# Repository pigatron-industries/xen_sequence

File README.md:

# xen_sequence
MIDI hardware sequencer

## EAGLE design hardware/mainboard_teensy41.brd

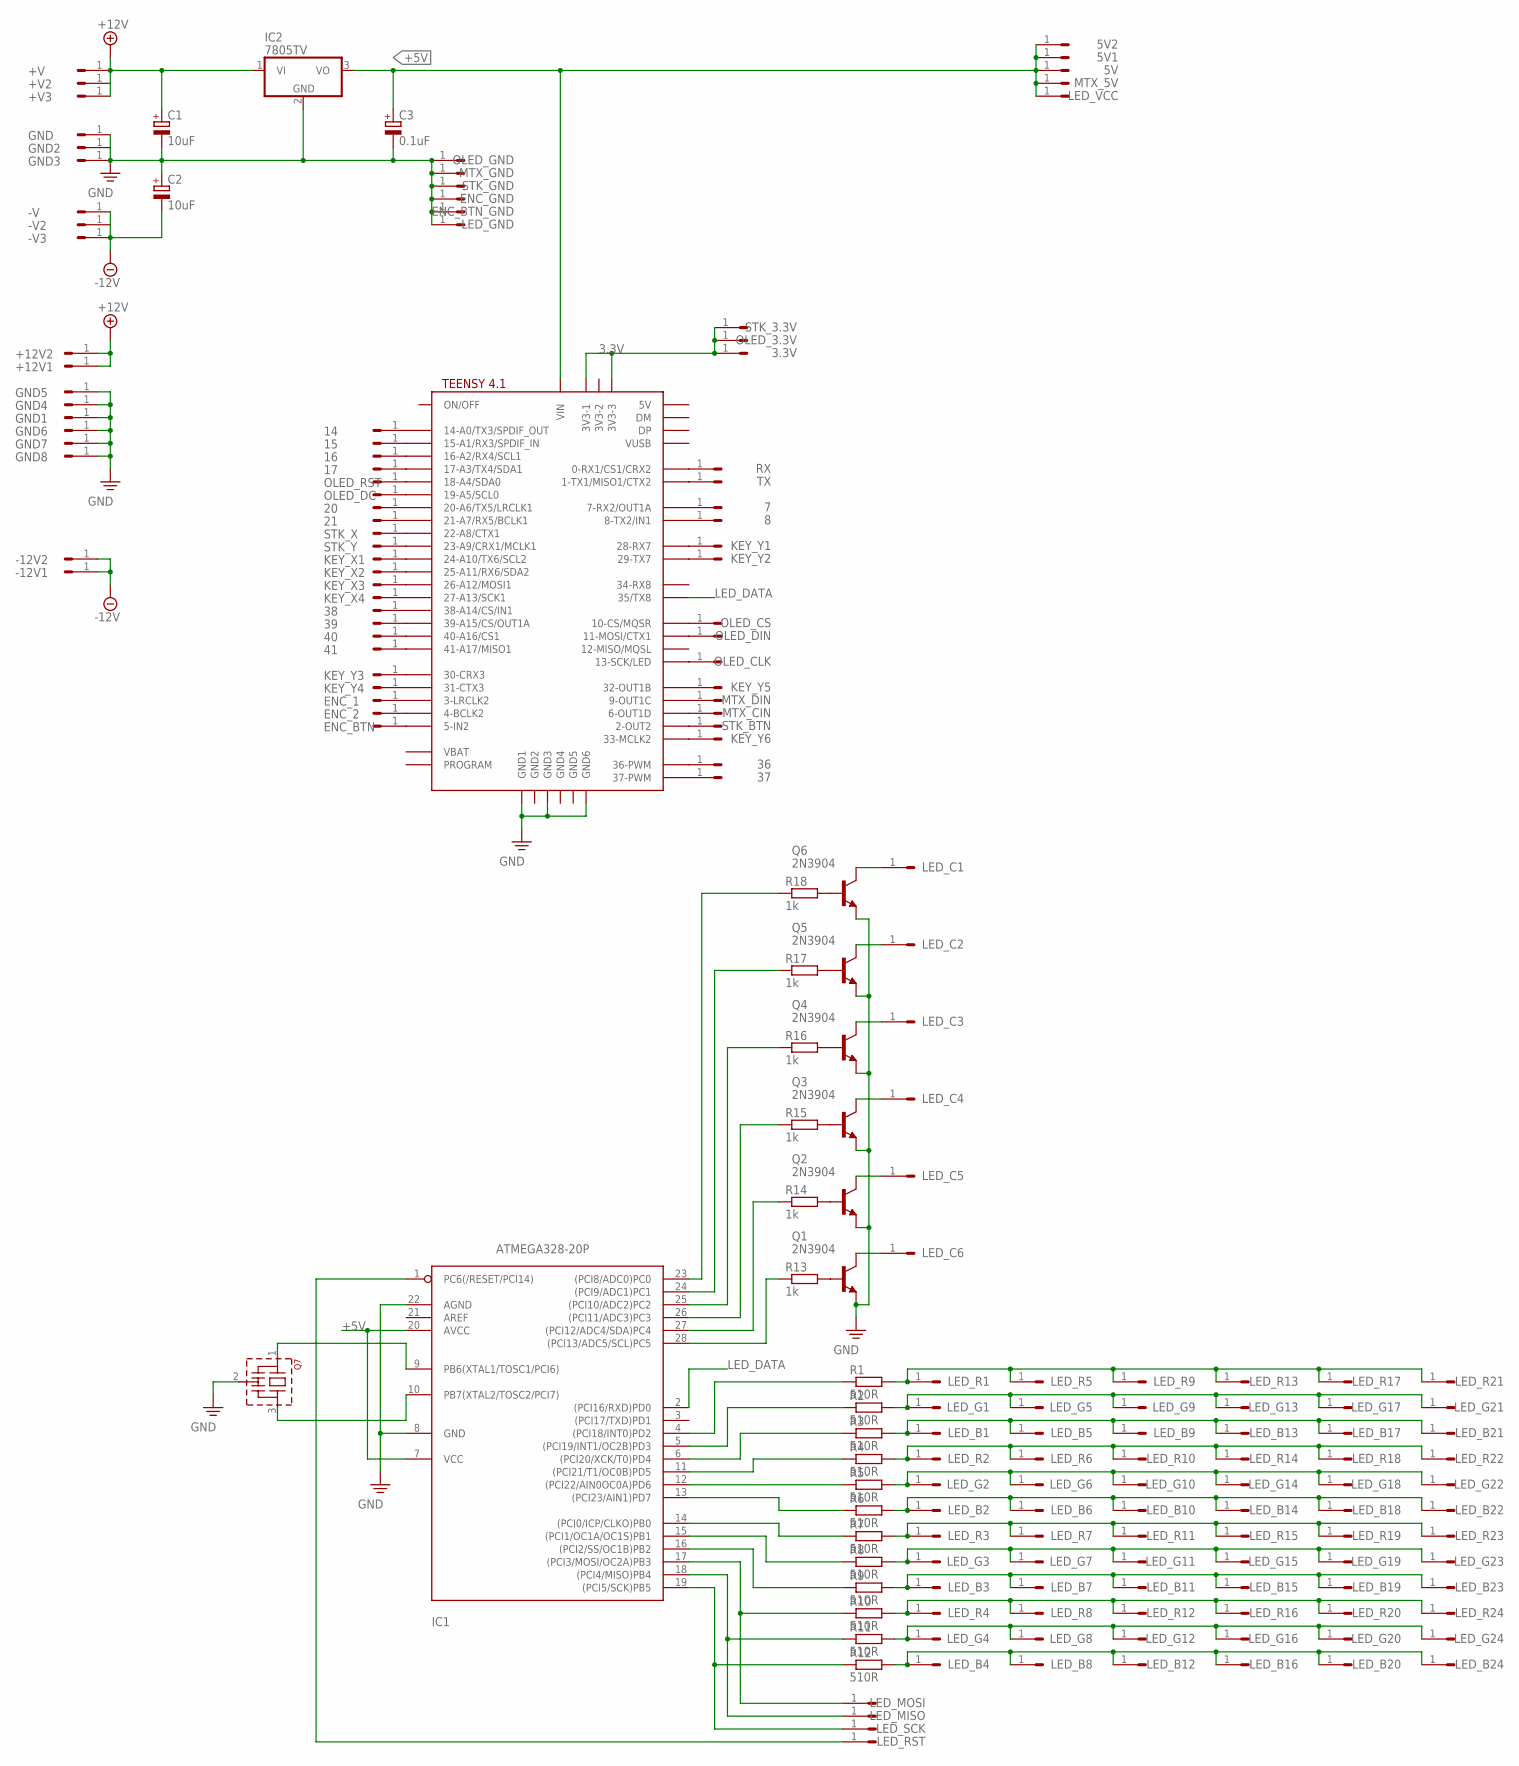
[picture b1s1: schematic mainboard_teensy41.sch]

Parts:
3.3V, 5V, 5V1, 5V2, 7, 8, 14, 15, 16, 17, 20, 21, 36, 37, 38, 39, 40, 41: HEADER/MALE/01
+12V1, +12V2: HEADER/MALE/01
+V, +V2, +V3: HEADER/MALE/01
-12V1, -12V2: HEADER/MALE/01
-V, -V2, -V3: HEADER/MALE/01
C1, C2: 10uF; E2,5-6
C3: 0.1uF; E2,5-6
ENC_1, ENC_2: HEADER/MALE/01
ENC_BTN: HEADER/MALE/01
ENC_BTN_GND: HEADER/MALE/01
ENC_GND: HEADER/MALE/01
GND, GND1, GND2, GND3, GND4, GND5, GND6, GND7, GND8: HEADER/MALE/01
IC1: ATMEGA328-20P; DIL28-3
IC2: 7805TV; TO220V
KEY_X1, KEY_X2, KEY_X3, KEY_X4: HEADER/MALE/01
KEY_Y1, KEY_Y2, KEY_Y3, KEY_Y4, KEY_Y5, KEY_Y6: HEADER/MALE/01
LED_B1, LED_B2, LED_B3, LED_B4, LED_B5, LED_B6, LED_B7, LED_B8, LED_B9, LED_B10, LED_B11, LED_B12, LED_B13, LED_B14, LED_B15, LED_B16, LED_B17, LED_B18, LED_B19, LED_B20, LED_B21, LED_B22, LED_B23, LED_B24: HEADER/MALE/01
LED_C1, LED_C2, LED_C3, LED_C4, LED_C5, LED_C6: HEADER/MALE/01
LED_G1, LED_G2, LED_G3, LED_G4, LED_G5, LED_G6, LED_G7, LED_G8, LED_G9, LED_G10, LED_G11, LED_G12, LED_G13, LED_G14, LED_G15, LED_G16, LED_G17, LED_G18, LED_G19, LED_G20, LED_G21, LED_G22, LED_G23, LED_G24: HEADER/MALE/01
LED_GND: HEADER/MALE/01
LED_MISO: HEADER/MALE/01
LED_MOSI: HEADER/MALE/01
LED_R1, LED_R2, LED_R3, LED_R4, LED_R5, LED_R6, LED_R7, LED_R8, LED_R9, LED_R10, LED_R11, LED_R12, LED_R13, LED_R14, LED_R15, LED_R16, LED_R17, LED_R18, LED_R19, LED_R20, LED_R21, LED_R22, LED_R23, LED_R24: HEADER/MALE/01
LED_RST: HEADER/MALE/01
LED_SCK: HEADER/MALE/01
LED_VCC: HEADER/MALE/01
MTX_5V: HEADER/MALE/01
MTX_CIN: HEADER/MALE/01
MTX_DIN: HEADER/MALE/01
MTX_GND: HEADER/MALE/01
OLED_3.3V: HEADER/MALE/01
OLED_CLK: HEADER/MALE/01
OLED_CS: HEADER/MALE/01
OLED_DC: HEADER/MALE/01
OLED_DIN: HEADER/MALE/01
OLED_GND: HEADER/MALE/01
OLED_RST: HEADER/MALE/01
Q1, Q2, Q3, Q4, Q5, Q6: 2N3904; TO92
Q7: CSTLS_G; CSTLS_G8
R1, R2, R3, R4, R5, R6, R7, R8, R9, R10, R11, R12: 510R; RESISTOR/7.5
R13, R14, R15, R16, R17, R18: 1k; RESISTOR/7.5
RX: HEADER/MALE/01
STK_3.3V: HEADER/MALE/01
STK_BTN: HEADER/MALE/01
STK_GND: HEADER/MALE/01
STK_X: HEADER/MALE/01
STK_Y: HEADER/MALE/01
TX: HEADER/MALE/01
U$1: TEENSY41-E; TENNSY41-E

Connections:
3.3V: 3.3V.1, OLED_3.3V.1, STK_3.3V.1, U$1.3V3-1, U$1.3V3-3
+5V: 5V.1, 5V1.1, 5V2.1, C3.+, IC1.7 (VCC), IC1.20 (AVCC), IC2.3 (VO), LED_VCC.1, MTX_5V.1, U$1.VIN
+12V: +12V1.1, +12V2.1, +V.1, +V2.1, +V3.1, C1.+, IC2.1 (VI)
-12V: -12V1.1, -12V2.1, -V.1, -V2.1, -V3.1, C2.-
GND: C1.-, C2.+, C3.-, ENC_BTN_GND.1, ENC_GND.1, GND.1, GND1.1, GND2.1, GND3.1, GND4.1, GND5.1, GND6.1, GND7.1, GND8.1, IC1.8 (GND), IC1.22 (AGND), IC2.2 (GND), LED_GND.1, MTX_GND.1, OLED_GND.1, Q1.3 (E), Q2.3 (E), Q3.3 (E), Q4.3 (E), Q5.3 (E), Q6.3 (E), Q7.2 (VSS), STK_GND.1, U$1.GND1, U$1.GND3, U$1.GND6
LED_DATA: IC1.2 ((PCI16/RXD)PD0), U$1.35-TX8 (35/TX8)
unnamed: IC1.4 ((PCI18/INT0)PD2), R1.1
unnamed: OLED_CS.1, U$1.10-CS\MQSR (10-CS/MQSR)
unnamed: OLED_DIN.1, U$1.11-MOSI/CTX1
unnamed: OLED_CLK.1, U$1.13-SCK/LED
unnamed: RX.1, U$1.0-RX1/CS1/CRX2
unnamed: TX.1, U$1.1-TX1/MISO1/CTX2
unnamed: KEY_X1.1, U$1.24-A10/TX6/SCL2
unnamed: KEY_X2.1, U$1.25-A11/RX6/SDA2
unnamed: KEY_Y1.1, U$1.28-RX7
unnamed: KEY_Y2.1, U$1.29-TX7
unnamed: KEY_Y5.1, U$1.32-OUT1B
unnamed: KEY_X3.1, U$1.26-A12/MOSI1
unnamed: MTX_CIN.1, U$1.6-OUT1D
unnamed: STK_BTN.1, U$1.2-OUT2
unnamed: KEY_Y6.1, U$1.33-MCLK2
unnamed: KEY_Y3.1, U$1.30-CRX3
unnamed: KEY_Y4.1, U$1.31-CTX3
unnamed: ENC_1.1, U$1.3-LRCLK2
unnamed: ENC_2.1, U$1.4-BCLK2
unnamed: ENC_BTN.1, U$1.5-IN2
unnamed: KEY_X4.1, U$1.27-A13/SCK1
unnamed: STK_X.1, U$1.22-A8/CTX1
unnamed: STK_Y.1, U$1.23-A9/CRX1/MCLK1
unnamed: OLED_RST.1, U$1.18-A4/SDA0
unnamed: OLED_DC.1, U$1.19-A5/SCL0
unnamed: 14.1, U$1.14-A0/TX3/SPDIF_OUT
unnamed: IC1.5 ((PCI19/INT1/OC2B)PD3), R2.1
unnamed: IC1.6 ((PCI20/XCK/T0)PD4), R3.1
unnamed: IC1.11 ((PCI21/T1/OC0B)PD5), R4.1
unnamed: IC1.12 ((PCI22/AIN0OC0A)PD6), R5.1
unnamed: IC1.13 ((PCI23/AIN1)PD7), R6.1
unnamed: IC1.14 ((PCI0/ICP/CLKO)PB0), R7.1
unnamed: IC1.15 ((PCI1/OC1A/OC1S)PB1), R8.1
unnamed: IC1.16 ((PCI2/SS/OC1B)PB2), R9.1
unnamed: IC1.17 ((PCI3/MOSI/OC2A)PB3), LED_MOSI.1, R10.1
unnamed: IC1.18 ((PCI4/MISO)PB4), LED_MISO.1, R11.1
unnamed: 15.1, U$1.15-A1/RX3/SPDIF_IN
unnamed: IC1.1 (PC6(/RESET/PCI14)), LED_RST.1
unnamed: LED_R1.1, LED_R5.1, LED_R9.1, LED_R13.1, LED_R17.1, LED_R21.1, R1.2
unnamed: LED_G1.1, LED_G5.1, LED_G9.1, LED_G13.1, LED_G17.1, LED_G21.1, R2.2
unnamed: LED_B1.1, LED_B5.1, LED_B9.1, LED_B13.1, LED_B17.1, LED_B21.1, R3.2
unnamed: LED_R2.1, LED_R6.1, LED_R10.1, LED_R14.1, LED_R18.1, LED_R22.1, R4.2
unnamed: LED_G2.1, LED_G6.1, LED_G10.1, LED_G14.1, LED_G18.1, LED_G22.1, R5.2
unnamed: LED_B2.1, LED_B6.1, LED_B10.1, LED_B14.1, LED_B18.1, LED_B22.1, R6.2
unnamed: LED_R3.1, LED_R7.1, LED_R11.1, LED_R15.1, LED_R19.1, LED_R23.1, R7.2
unnamed: LED_G3.1, LED_G7.1, LED_G11.1, LED_G15.1, LED_G19.1, LED_G23.1, R8.2
unnamed: LED_B3.1, LED_B7.1, LED_B11.1, LED_B15.1, LED_B19.1, LED_B23.1, R9.2
unnamed: LED_R4.1, LED_R8.1, LED_R12.1, LED_R16.1, LED_R20.1, LED_R24.1, R10.2
unnamed: LED_G4.1, LED_G8.1, LED_G12.1, LED_G16.1, LED_G20.1, LED_G24.1, R11.2
unnamed: LED_B4.1, LED_B8.1, LED_B12.1, LED_B16.1, LED_B20.1, LED_B24.1, R12.2
unnamed: Q1.2 (B), R13.2
unnamed: IC1.28 ((PCI13/ADC5/SCL)PC5), R13.1
unnamed: Q2.2 (B), R14.2
unnamed: Q3.2 (B), R15.2
unnamed: Q4.2 (B), R16.2
unnamed: Q5.2 (B), R17.2
unnamed: Q6.2 (B), R18.2
unnamed: IC1.27 ((PCI12/ADC4/SDA)PC4), R14.1
unnamed: IC1.26 ((PCI11/ADC3)PC3), R15.1
unnamed: IC1.25 ((PCI10/ADC2)PC2), R16.1
unnamed: IC1.24 ((PCI9/ADC1)PC1), R17.1
unnamed: IC1.23 ((PCI8/ADC0)PC0), R18.1
unnamed: LED_C1.1, Q6.1 (C)
unnamed: LED_C2.1, Q5.1 (C)
unnamed: LED_C3.1, Q4.1 (C)
unnamed: 36.1, U$1.36-PWM
unnamed: 37.1, U$1.37-PWM
unnamed: LED_C4.1, Q3.1 (C)
unnamed: LED_C5.1, Q2.1 (C)
unnamed: LED_C6.1, Q1.1 (C)
unnamed: 16.1, U$1.16-A2/RX4/SCL1
unnamed: 17.1, U$1.17-A3/TX4/SDA1
unnamed: 7.1, U$1.7-RX2/OUT1A
unnamed: 8.1, U$1.8-TX2/IN1
unnamed: 20.1, U$1.20-A6/TX5/LRCLK1
unnamed: 21.1, U$1.21-A7/RX5/BCLK1
unnamed: MTX_DIN.1, U$1.9-OUT1C
unnamed: 38.1, U$1.38-A14/CS/IN1
unnamed: 39.1, U$1.39-A15/CS/OUT1A
unnamed: 40.1, U$1.40-A16/CS1
unnamed: 41.1, U$1.41-A17/MISO1
unnamed: IC1.9 (PB6(XTAL1/TOSC1/PCI6)), Q7.1
unnamed: IC1.10 (PB7(XTAL2/TOSC2/PCI7)), Q7.3
unnamed: IC1.19 ((PCI5/SCK)PB5), LED_SCK.1, R12.1

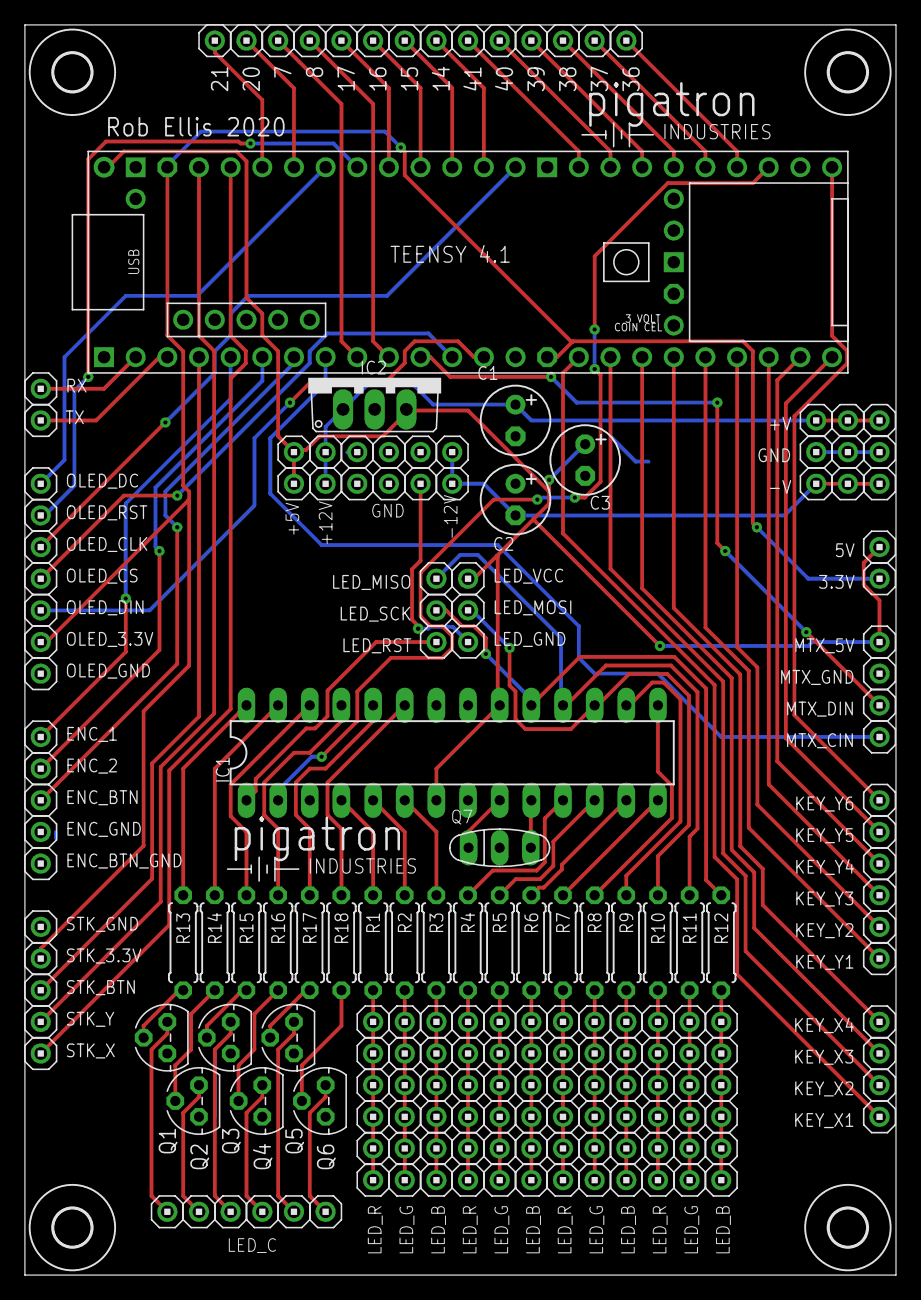
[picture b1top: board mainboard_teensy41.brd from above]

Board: 2 copper layers, 69.9 x 100.3 mm, 191 parts (0 on the bottom side), 90 nets.

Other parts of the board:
U$2, U$3, U$4, U$7: STANDOFF/3.0
U$5, U$8: PIGATRON-LOGO

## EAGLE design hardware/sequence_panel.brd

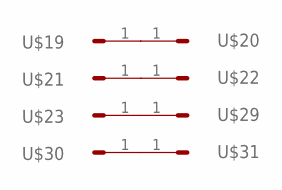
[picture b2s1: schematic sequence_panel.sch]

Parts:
U$19, U$20, U$21, U$22, U$23, U$29, U$30, U$31: HEADER/MALE/01

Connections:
unnamed: U$19.1, U$20.1
unnamed: U$21.1, U$22.1
unnamed: U$23.1, U$29.1
unnamed: U$30.1, U$31.1

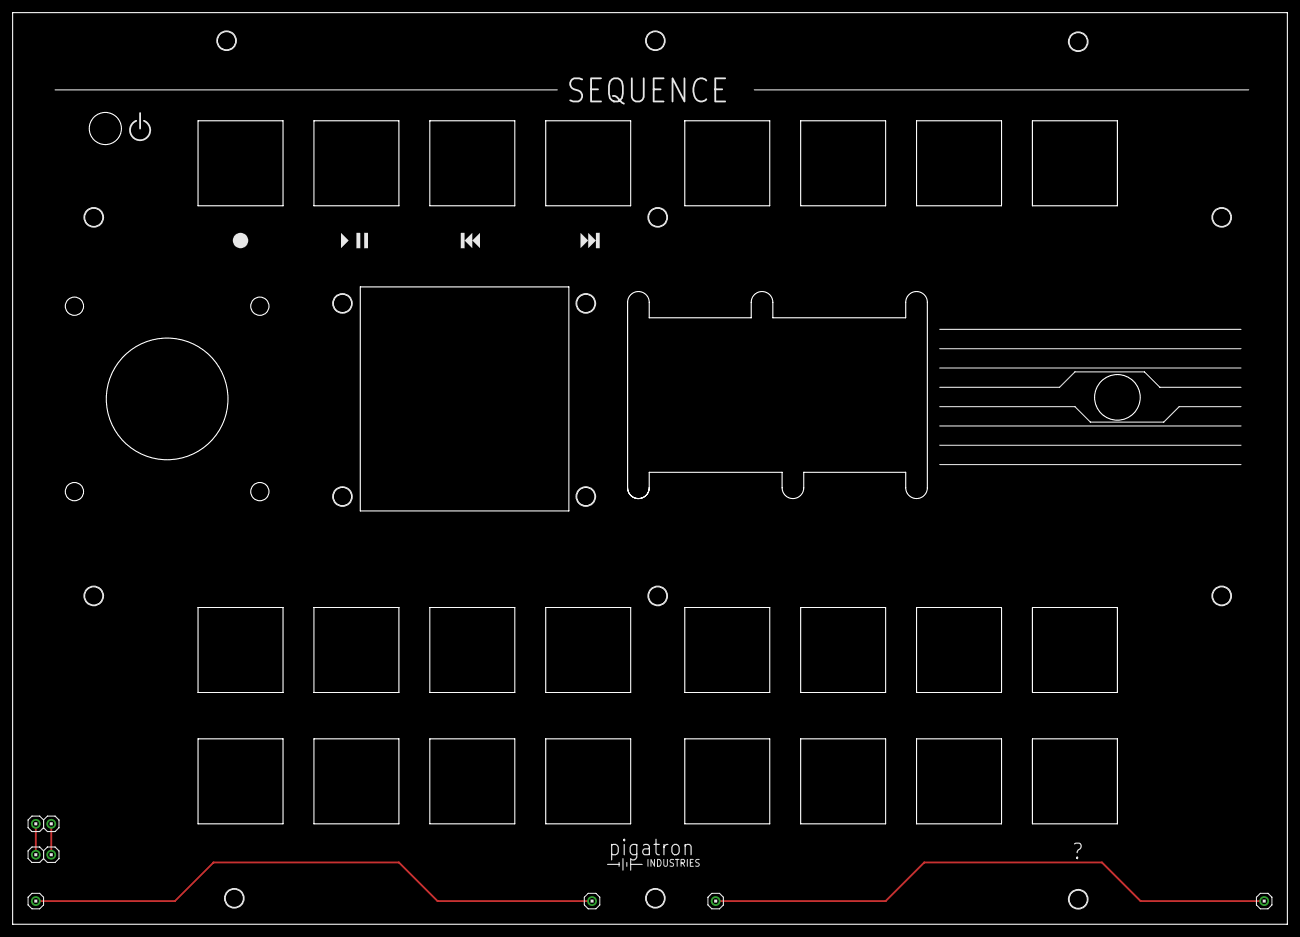
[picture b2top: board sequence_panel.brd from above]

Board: 2 copper layers, 209.6 x 149.9 mm, 26 parts (1 on the bottom side), 4 nets.

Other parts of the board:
U$1, U$2, U$3, U$4, U$5, U$6, U$7, U$8, U$9, U$10, U$11, U$12, U$15, U$16, U$17, U$18: STANDOFF/3.0
U$13, U$14: PIGATRON-LOGO

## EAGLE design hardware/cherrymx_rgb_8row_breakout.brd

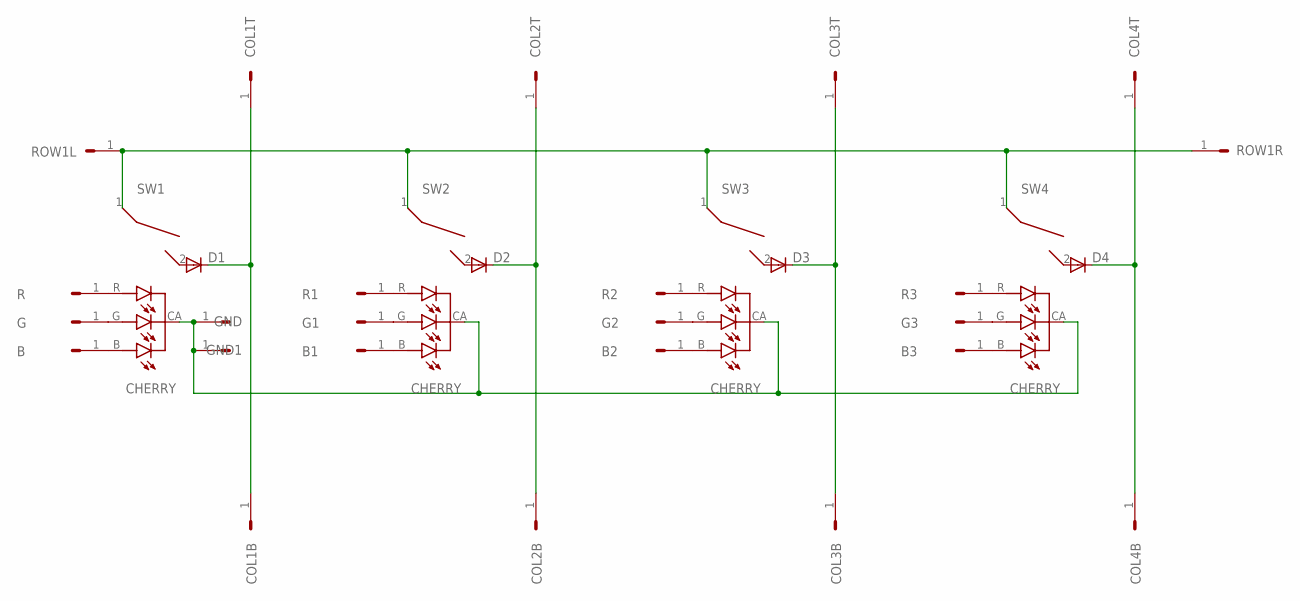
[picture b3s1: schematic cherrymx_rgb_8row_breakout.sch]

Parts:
B, B1, B2, B3: HEADER/MALE/01
COL1B, COL1T, COL2B, COL2T, COL3B, COL3T, COL4B, COL4T: HEADER/MALE/01
D1, D2, D3, D4: 1N4148DO35-7; DO35-7
G, G1, G2, G3: HEADER/MALE/01
GND, GND1: HEADER/MALE/01
R, R1, R2, R3: HEADER/MALE/01
ROW1L, ROW1R: HEADER/MALE/01
SW1, SW2, SW3, SW4: CHERRY; SWITCH_CHERRY_MX_RGB

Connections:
unnamed: D1.A, SW1.2
unnamed: B.1, SW1.B (B-CAT)
unnamed: G.1, SW1.G (G-CAT)
unnamed: R.1, SW1.R (R-CAT)
unnamed: COL1B.1, COL1T.1, D1.C
unnamed: GND.1, GND1.1, SW1.CA (COMMON-ANODE), SW2.CA (COMMON-ANODE), SW3.CA (COMMON-ANODE), SW4.CA (COMMON-ANODE)
unnamed: B1.1, SW2.B (B-CAT)
unnamed: G1.1, SW2.G (G-CAT)
unnamed: R1.1, SW2.R (R-CAT)
unnamed: D2.A, SW2.2
unnamed: COL2B.1, COL2T.1, D2.C
unnamed: B2.1, SW3.B (B-CAT)
unnamed: G2.1, SW3.G (G-CAT)
unnamed: R2.1, SW3.R (R-CAT)
unnamed: D3.A, SW3.2
unnamed: COL3B.1, COL3T.1, D3.C
unnamed: B3.1, SW4.B (B-CAT)
unnamed: G3.1, SW4.G (G-CAT)
unnamed: R3.1, SW4.R (R-CAT)
unnamed: D4.A, SW4.2
unnamed: COL4B.1, COL4T.1, D4.C
unnamed: ROW1L.1, ROW1R.1, SW1.1, SW2.1, SW3.1, SW4.1

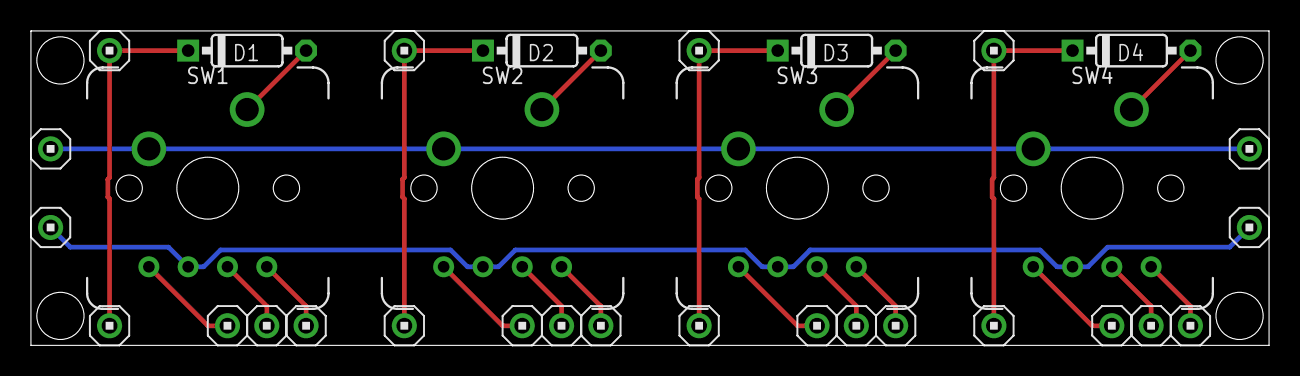
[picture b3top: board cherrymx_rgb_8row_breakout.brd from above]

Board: 2 copper layers, 80.0 x 20.3 mm, 32 parts (0 on the bottom side), 22 nets.

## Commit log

2020-05-26 Adde eagle files to .gitignore
2020-05-26 Added basic structure and task manger
2020-05-26 Added empty sequencer class
2020-06-02 Start of sequence display interface + analog stick driver.
2020-06-02 Ananlog stick controls cursor
2020-06-02 Scroll sequence left and right when cursor moves off edge
2020-06-02 Added grid numbers where status bar was
2020-06-03 Show sequence data in LED matrix
2020-06-04 remove .clang_complete
2020-06-04 Moved to platform io file structure
2020-06-04 Deleted ino file
2020-06-04 Incresed stick sensitivity + exapnded led matrix to 16 columns
2020-06-04 Switch between views when pressing analog stick
2020-06-04 render cursor on led matrix
2020-06-04 Added play head position to led matrix
2020-06-05 Added parameter list
2020-06-05 Seperated field rendering into sperate class
2020-06-06 Use encoder button to switch between parameter views
2020-06-06 Make selection led slightly brighter when it is active
2020-06-06 Show channel selection using all leds in channel
2020-06-06 Added min and max to integer fields
2020-06-06 Added unit string to integer field
2020-06-06 Added boolean paramter type
2020-06-07 Added velocity field
2020-06-07 Refactored data structure
2020-06-07 Update bar field data from model
2020-06-07 Update field values based on selected data
2020-06-07 Added methods to add new event to pattern
2020-06-09 Handle key matrix presses + handle add event key press
2020-06-09 Save event field data updates to model
2020-06-10 Back button goes back to main sequence view
2020-06-10 moved key pin definition to hwconfig.h
2020-06-10 Implemented sequencer clock
2020-06-10 render play position on led matrix
2020-06-10 BPM changes reflected while playing
2020-06-13 CAdded interface event class with data. Removed buffering of display
2020-06-13 added break into cases
2020-06-13 Made rendering of parameter view more efficient
2020-06-14 renamed modules to sequencer
2020-06-14 Added midi output code
2020-06-28 Compile events into lists of midi messages
2020-06-28 Removed serial.println
2020-07-01 Added libraries to ini file
2020-07-13 Added source for seperate led matrix driver using atmega328p
2020-08-08 Created custom SPISlave class to use 2 pins only
2020-08-30 Use serial to communicate with keyboard led driver
2020-10-28 Allow mutliple keypressed at once
2020-11-21 Corrected midi message order
2020-11-21 Moved display and matrix to static hardware classs
2020-11-21 UI Changes
2020-11-21 Change selected event when moving cursor up/down
2020-11-22 Added help pages + sd card initialisation
2020-11-23 File view page
2020-11-23 Changed current directory to String
2020-11-29 Fixed bug in file loading
2020-11-30 Refactor of ui components
2020-11-30 Moved file
2020-12-02 Made file list selectable
2020-12-05 press stick to change selection mode
2020-12-05 refactor of render functions
2020-12-06 load and save data from selected file
2020-12-08 Serialize sequence to json
2020-12-12 Add new bar when one doesn't exist
2020-12-12 Load sequence from file
2020-12-19 Clear keyboard leds when switching from file view
2020-12-20 Confirm load/save dialog
2020-12-21 Read midi input and store in sequence
2020-12-22 record midi note on into currently selected event
2020-12-22 Add new event if note on recieved and no event selected
2020-12-22 Output midi clock
2020-12-22 Send system stop event
2020-12-24 Move between bars using next and prev keys
2020-12-24 stop cursor scrolling past last bar
2020-12-25 Copy and paste event
2020-12-25 Make actual copiy of copied event so if original is delted then copy is still useable
2020-12-26 Drag and drop event
2020-12-26 Add and remove existing patterns in sequence view
2020-12-26 Change pattern number using data encoder
2020-12-27 Copy and paste in sequence view
2020-12-27 Move pattern in sequence view
2020-12-27 Add [NEW FILE] item
2020-12-31 Create new files and delete files
2021-02-07 Tidy up includes
2021-02-07 Show note names instead of numbers
2021-02-23 Fixed bug where first note is not played
2021-02-23 play currently slected bar
2021-02-23 initialise view after loading file
2021-02-23 Keep file selection
2021-02-23 render after dropping
2021-02-24 Switch loop modes
2021-02-24 Auto load last sequence
2021-02-24 Draw pattern being dragged
2021-02-24 Nudge bars left/right
2021-02-26 Clear bar numbers when rendering
2021-02-27 Decrement and increment pattern also adds and removes patterns
2021-03-06 Clear sequence
2021-03-07 Clear whole pattern
2021-03-08 Change bpm of whole song + bpm multiplier
2021-03-14 Implemented more ways of moving /copying patterns
2021-03-14 Make copy of pattern
2021-03-14 show move mode in status bar
2021-03-17 Improve encodr lib
2021-03-17 Combined encoder driver into single class
2021-03-19 Highlight selected pattern number.
2021-03-20 Refactor field component to use GraphicsContext
2021-03-20 Use LIstComponent for parameter fields
2021-03-20 Refactored into seperate ParameterViews
2021-03-20 Further refactor into separate parameter views
2021-03-20 Made parameter view fields private
2021-03-21 Added function key to change move mode
2021-03-27 changd to multiple events per tick
2021-03-27 implmented SequenceTickEvents methods
2021-03-27 null check
2021-03-27 Move compilation unit to tick events instead of event.
2021-03-27 Abstract event and note on event
2021-03-28 Use encoder to scroll through selected field
2021-03-28 moce change selection mode function to parameter field
2021-03-28 Use single range field for on/off times
2021-03-28 Chnaged solid selction colour to outer rectangle
2021-03-29 rendeer range parameter as rectangle
2021-03-29 scale range properly for screen display
2021-03-29 scale range properly for display
2021-04-03 parameter view for multiple events
2021-04-03 Added line component
2021-04-10 moved copy paste keys to bottom row
2021-04-10 add and remove events from tick
2021-04-11 Make list component scrollable
2021-04-12 ControlEvent event type
2021-04-13 Rerender when changing event type
2021-04-13 improve RangeScale performance
2021-04-13 render using event queue
2021-04-13 use render queue instead of returning event type
2021-04-15 Sort midi events when compiling
2021-04-16 Changse to debuf logging
2021-04-22 Create new event on midi event if needed
2021-04-23 record control change messages by matching on control number
2021-05-25 Set event type field when changing event
2021-05-25 Display current loop mode
2021-05-25 Set record modes, moved playback modes to play button
2021-05-25 Default to event selection mode
2021-05-25 Advance on message record mode
2021-05-25 Advance to next note when all notes on channel are off
2021-05-25 Polyphonic recording
2021-05-28 Fix bug with paramters not showing
2021-05-28 Add midi channel parameter
2021-05-29 changed ppqn to 24
2021-05-30 Use interrupt timer for midi output
2021-06-20 Increment pulse and tick after playing note
2021-06-24 reset sequencer before playing
